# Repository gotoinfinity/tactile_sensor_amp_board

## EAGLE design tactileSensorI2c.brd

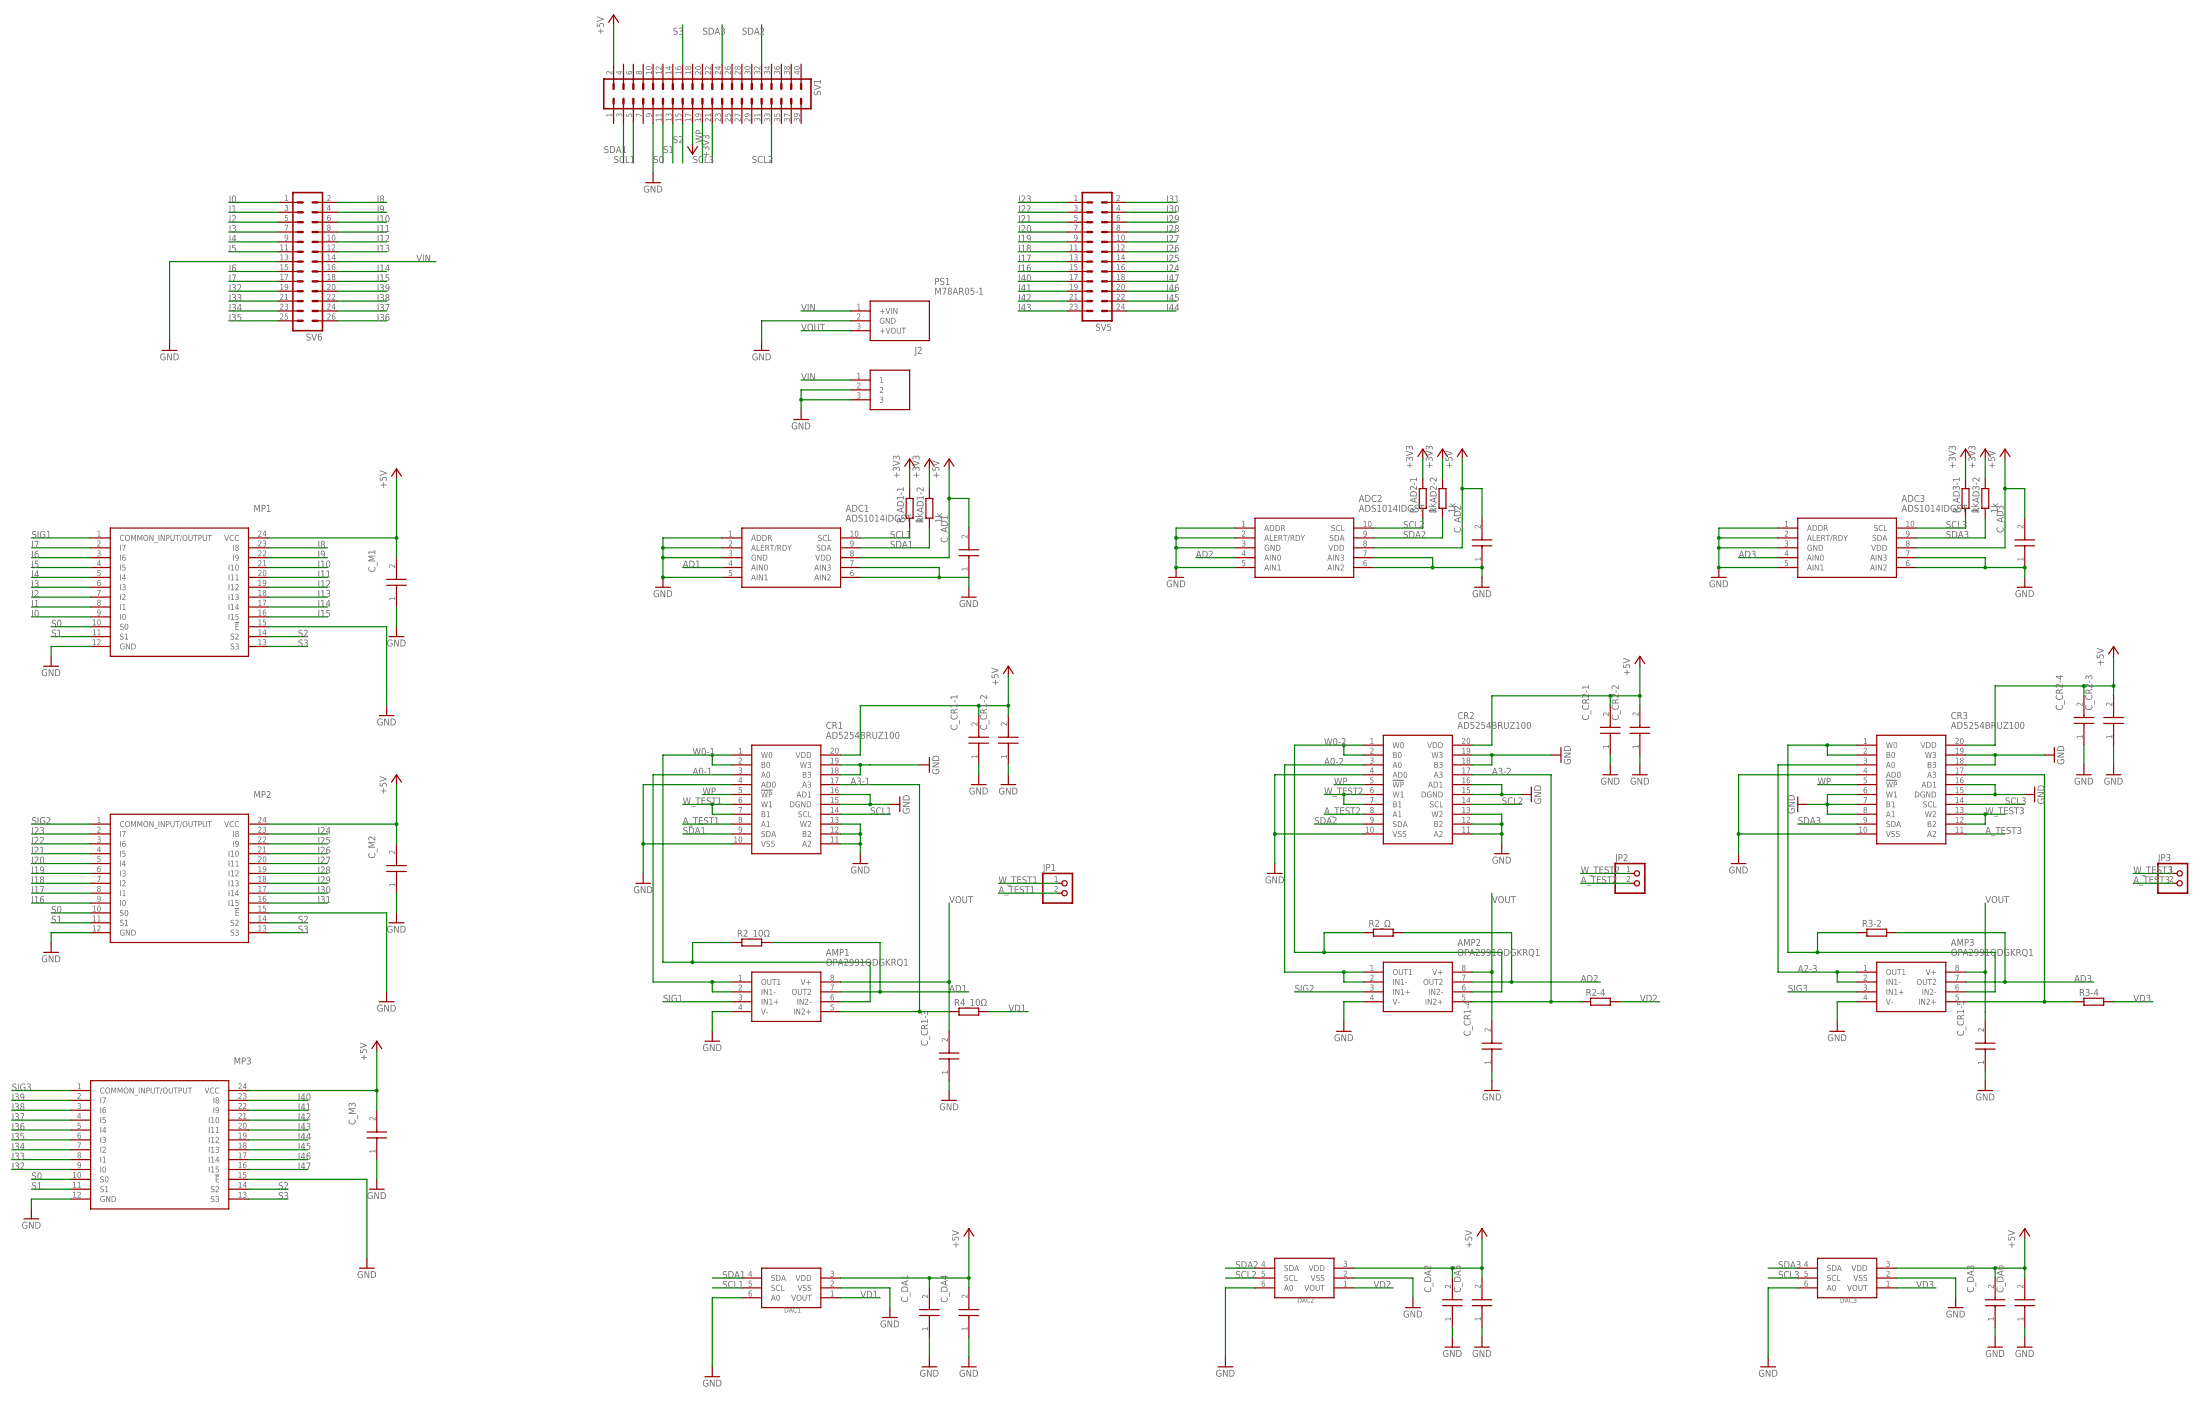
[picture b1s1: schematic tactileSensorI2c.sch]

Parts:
ADC1, ADC2, ADC3: ADS1014IDGST; SOP50P490X110-10N
AMP1, AMP2, AMP3: OPA2991QDGKRQ1; SOP65P490X110-8N
CR1, CR2, CR3: AD5254BRUZ100; SOP65P640X120-20N
C_AD1, C_AD2, C_AD3: 0.1u; CAPC2012X140N
C_CR1-1, C_CR2-1: 0.1u; CAPC2012X140N
C_CR1-2, C_CR1-3, C_CR1-4, C_CR1-5, C_CR2-2: 10u; CAPC2012X140N
C_CR2-3, C_CR2-4: C0805C105J3RACTU; CAPC2012X140N
C_DA1, C_DA2, C_DA3, C_DA4, C_DA5, C_DA6: C0805C105J3RACTU; CAPC2012X140N
C_M1, C_M2, C_M3: 0.1u; CAPC2012X140N
DAC1, DAC2, DAC3: MCP4725; SOT23-6
J2: 1725669
JP1, JP2, JP3: PINHD-1X2; 1X02
MP1, MP2, MP3: CD74HC4067SM96; SOP65P780X200-24N
PS1: M78AR05-1; M78AR05
R2-4, R2_10Ω, R2_Ω, R3-2, R3-4, R4_10Ω: R-EU_0204/2V; 0204V
R_AD1-1, R_AD1-2, R_AD2-1, R_AD2-2, R_AD3-1, R_AD3-2: 1k; R0805
SV1: MA20-2
SV5: MA12-2
SV6: MA13-2

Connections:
+3V3: R_AD1-1.2, R_AD1-2.2, R_AD2-1.2, R_AD2-2.2, R_AD3-1.2, R_AD3-2.2, SV1.17
+5V: ADC1.8 (VDD), ADC2.8 (VDD), ADC3.8 (VDD), CR1.20 (VDD), CR2.20 (VDD), CR3.20 (VDD), C_AD1.2, C_AD2.2, C_AD3.2, C_CR1-1.2, C_CR1-2.2, C_CR2-1.2, C_CR2-2.2, C_CR2-3.2, C_CR2-4.2, C_DA1.2, C_DA2.2, C_DA3.2, C_DA4.2, C_DA5.2, C_DA6.2, C_M1.2, C_M2.2, C_M3.2, DAC1.3 (VDD), DAC2.3 (VDD), DAC3.3 (VDD), MP1.24 (VCC), MP2.24 (VCC), MP3.24 (VCC), SV1.2
A0-1: AMP1.1 (OUT1), AMP1.2 (IN1-), CR1.3 (A0)
A0-2: AMP2.1 (OUT1), AMP2.2 (IN1-), CR2.3 (A0)
A1-3: AMP3.5 (IN2+), CR3.17 (A3), R3-4.1
A2-3: AMP3.1 (OUT1), AMP3.2 (IN1-), CR3.3 (A0)
A3-1: AMP1.5 (IN2+), CR1.17 (A3), R4_10Ω.1
A3-2: AMP2.5 (IN2+), CR2.17 (A3), R2-4.1
AD1: ADC1.4 (AIN0), AMP1.7 (OUT2), R2_10Ω.2
AD2: ADC2.4 (AIN0), AMP2.7 (OUT2), R2_Ω.2
AD3: ADC3.4 (AIN0), AMP3.7 (OUT2), R3-2.2
A_TEST1: CR1.8 (A1), JP1.2
A_TEST2: CR2.8 (A1), JP2.2
A_TEST3: CR3.11 (A2), JP3.2
GND: ADC1.1 (ADDR), ADC1.2 (ALERT/RDY), ADC1.3 (GND), ADC1.5 (AIN1), ADC1.6 (AIN2), ADC1.7 (AIN3), ADC2.1 (ADDR), ADC2.2 (ALERT/RDY), ADC2.3 (GND), ADC2.5 (AIN1), ADC2.6 (AIN2), ADC2.7 (AIN3), ADC3.1 (ADDR), ADC3.2 (ALERT/RDY), ADC3.3 (GND), ADC3.5 (AIN1), ADC3.6 (AIN2), ADC3.7 (AIN3), AMP1.4 (V-), AMP2.4 (V-), AMP3.4 (V-), CR1.4 (AD0), CR1.10 (VSS), CR1.11 (A2), CR1.12 (B2), CR1.13 (W2), CR1.15 (DGND), CR1.16 (AD1), CR1.18 (B3), CR1.19 (W3), CR2.4 (AD0), CR2.10 (VSS), CR2.11 (A2), CR2.12 (B2), CR2.13 (W2), CR2.15 (DGND), CR2.16 (AD1), CR2.18 (B3), CR2.19 (W3), CR3.4 (AD0), CR3.6 (W1), CR3.7 (B1), CR3.8 (A1), CR3.10 (VSS), CR3.15 (DGND), CR3.16 (AD1), CR3.18 (B3), CR3.19 (W3), C_AD1.1, C_AD2.1, C_AD3.1, C_CR1-1.1, C_CR1-2.1, C_CR1-3.1, C_CR1-4.1, C_CR1-5.1, C_CR2-1.1, C_CR2-2.1, C_CR2-3.1, C_CR2-4.1, C_DA1.1, C_DA2.1, C_DA3.1, C_DA4.1, C_DA5.1, C_DA6.1, C_M1.1, C_M2.1, C_M3.1, DAC1.2 (VSS), DAC1.6 (A0), DAC2.2 (VSS), DAC2.6 (A0), DAC3.2 (VSS), DAC3.6 (A0), J2.2, J2.3, MP1.12 (GND), MP1.15 (!E), MP2.12 (GND), MP2.15 (!E), MP3.12 (GND), MP3.15 (!E), PS1.2 (GND), SV1.9, SV6.13
I0: MP1.9 (I0), SV6.1
I1: MP1.8 (I1), SV6.3
I2: MP1.7 (I2), SV6.5
I3: MP1.6 (I3), SV6.7
I4: MP1.5 (I4), SV6.9
I5: MP1.4 (I5), SV6.11
I6: MP1.3 (I6), SV6.15
I7: MP1.2 (I7), SV6.17
I8: MP1.23 (I8), SV6.2
I9: MP1.22 (I9), SV6.4
I10: MP1.21 (I10), SV6.6
I11: MP1.20 (I11), SV6.8
I12: MP1.19 (I12), SV6.10
I13: MP1.18 (I13), SV6.12
I14: MP1.17 (I14), SV6.16
I15: MP1.16 (I15), SV6.18
I16: MP2.9 (I0), SV5.15
I17: MP2.8 (I1), SV5.13
I18: MP2.7 (I2), SV5.11
I19: MP2.6 (I3), SV5.9
I20: MP2.5 (I4), SV5.7
I21: MP2.4 (I5), SV5.5
I22: MP2.3 (I6), SV5.3
I23: MP2.2 (I7), SV5.1
I24: MP2.23 (I8), SV5.16
I25: MP2.22 (I9), SV5.14
I26: MP2.21 (I10), SV5.12
I27: MP2.20 (I11), SV5.10
I28: MP2.19 (I12), SV5.8
I29: MP2.18 (I13), SV5.6
I30: MP2.17 (I14), SV5.4
I31: MP2.16 (I15), SV5.2
I32: MP3.9 (I0), SV6.19
I33: MP3.8 (I1), SV6.21
I34: MP3.7 (I2), SV6.23
I35: MP3.6 (I3), SV6.25
I36: MP3.5 (I4), SV6.26
I37: MP3.4 (I5), SV6.24
I38: MP3.3 (I6), SV6.22
I39: MP3.2 (I7), SV6.20
I40: MP3.23 (I8), SV5.17
I41: MP3.22 (I9), SV5.19
I42: MP3.21 (I10), SV5.21
I43: MP3.20 (I11), SV5.23
I44: MP3.19 (I12), SV5.24
I45: MP3.18 (I13), SV5.22
I46: MP3.17 (I14), SV5.20
I47: MP3.16 (I15), SV5.18
S0: MP1.10 (S0), MP2.10 (S0), MP3.10 (S0), SV1.11
S1: MP1.11 (S1), MP2.11 (S1), MP3.11 (S1), SV1.13
S2: MP1.14 (S2), MP2.14 (S2), MP3.14 (S2), SV1.15
S3: MP1.13 (S3), MP2.13 (S3), MP3.13 (S3), SV1.16
SCL1: ADC1.10 (SCL), CR1.14 (SCL), DAC1.5 (SCL), R_AD1-1.1, SV1.5
SCL2: ADC2.10 (SCL), CR2.14 (SCL), DAC2.5 (SCL), R_AD2-1.1, SV1.33
SCL3: ADC3.10 (SCL), CR3.14 (SCL), DAC3.5 (SCL), R_AD3-1.1, SV1.21
SDA1: ADC1.9 (SDA), CR1.9 (SDA), DAC1.4 (SDA), R_AD1-2.1, SV1.3
SDA2: ADC2.9 (SDA), CR2.9 (SDA), DAC2.4 (SDA), R_AD2-2.1, SV1.32
SDA3: ADC3.9 (SDA), CR3.9 (SDA), DAC3.4 (SDA), R_AD3-2.1, SV1.24
SIG1: AMP1.3 (IN1+), MP1.1 (COMMON_INPUT/OUTPUT)
SIG2: AMP2.3 (IN1+), MP2.1 (COMMON_INPUT/OUTPUT)
SIG3: AMP3.3 (IN1+), MP3.1 (COMMON_INPUT/OUTPUT)
VD1: DAC1.1 (VOUT), R4_10Ω.2
VD2: DAC2.1 (VOUT), R2-4.2
VD3: DAC3.1 (VOUT), R3-4.2
VIN: J2.1, PS1.1 (+VIN), SV6.14
VOUT: AMP1.8 (V+), AMP2.8 (V+), AMP3.8 (V+), C_CR1-3.2, C_CR1-4.2, C_CR1-5.2, PS1.3 (+VOUT)
W0-1: AMP1.6 (IN2-), CR1.1 (W0), CR1.2 (B0), R2_10Ω.1
W0-2: AMP2.6 (IN2-), CR2.1 (W0), CR2.2 (B0), R2_Ω.1
W1-3: AMP3.6 (IN2-), CR3.1 (W0), CR3.2 (B0), R3-2.1
WP: CR1.5 (!WP), CR2.5 (!WP), CR3.5 (!WP), SV1.19
W_TEST1: CR1.6 (W1), CR1.7 (B1), JP1.1
W_TEST2: CR2.6 (W1), CR2.7 (B1), JP2.1
W_TEST3: CR3.12 (B2), CR3.13 (W2), JP3.1

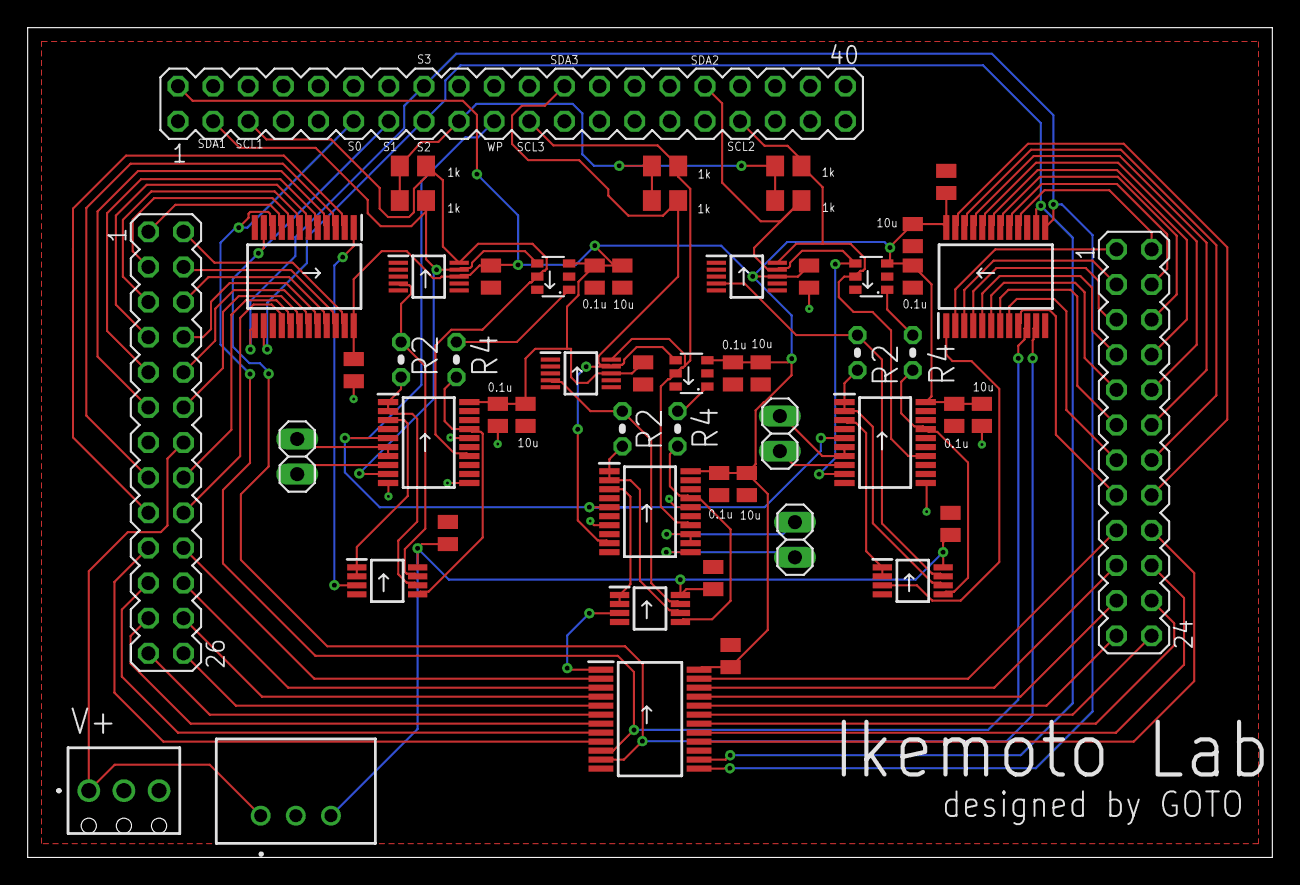
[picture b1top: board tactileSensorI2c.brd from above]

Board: 2 copper layers, 90.0 x 60.0 mm, 56 parts (0 on the bottom side), 88 nets.

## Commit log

2022-05-13 upload files
